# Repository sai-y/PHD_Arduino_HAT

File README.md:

# PHD_Arduino_HAT

Arduino Leonardo HAT for the Raspberry Pi

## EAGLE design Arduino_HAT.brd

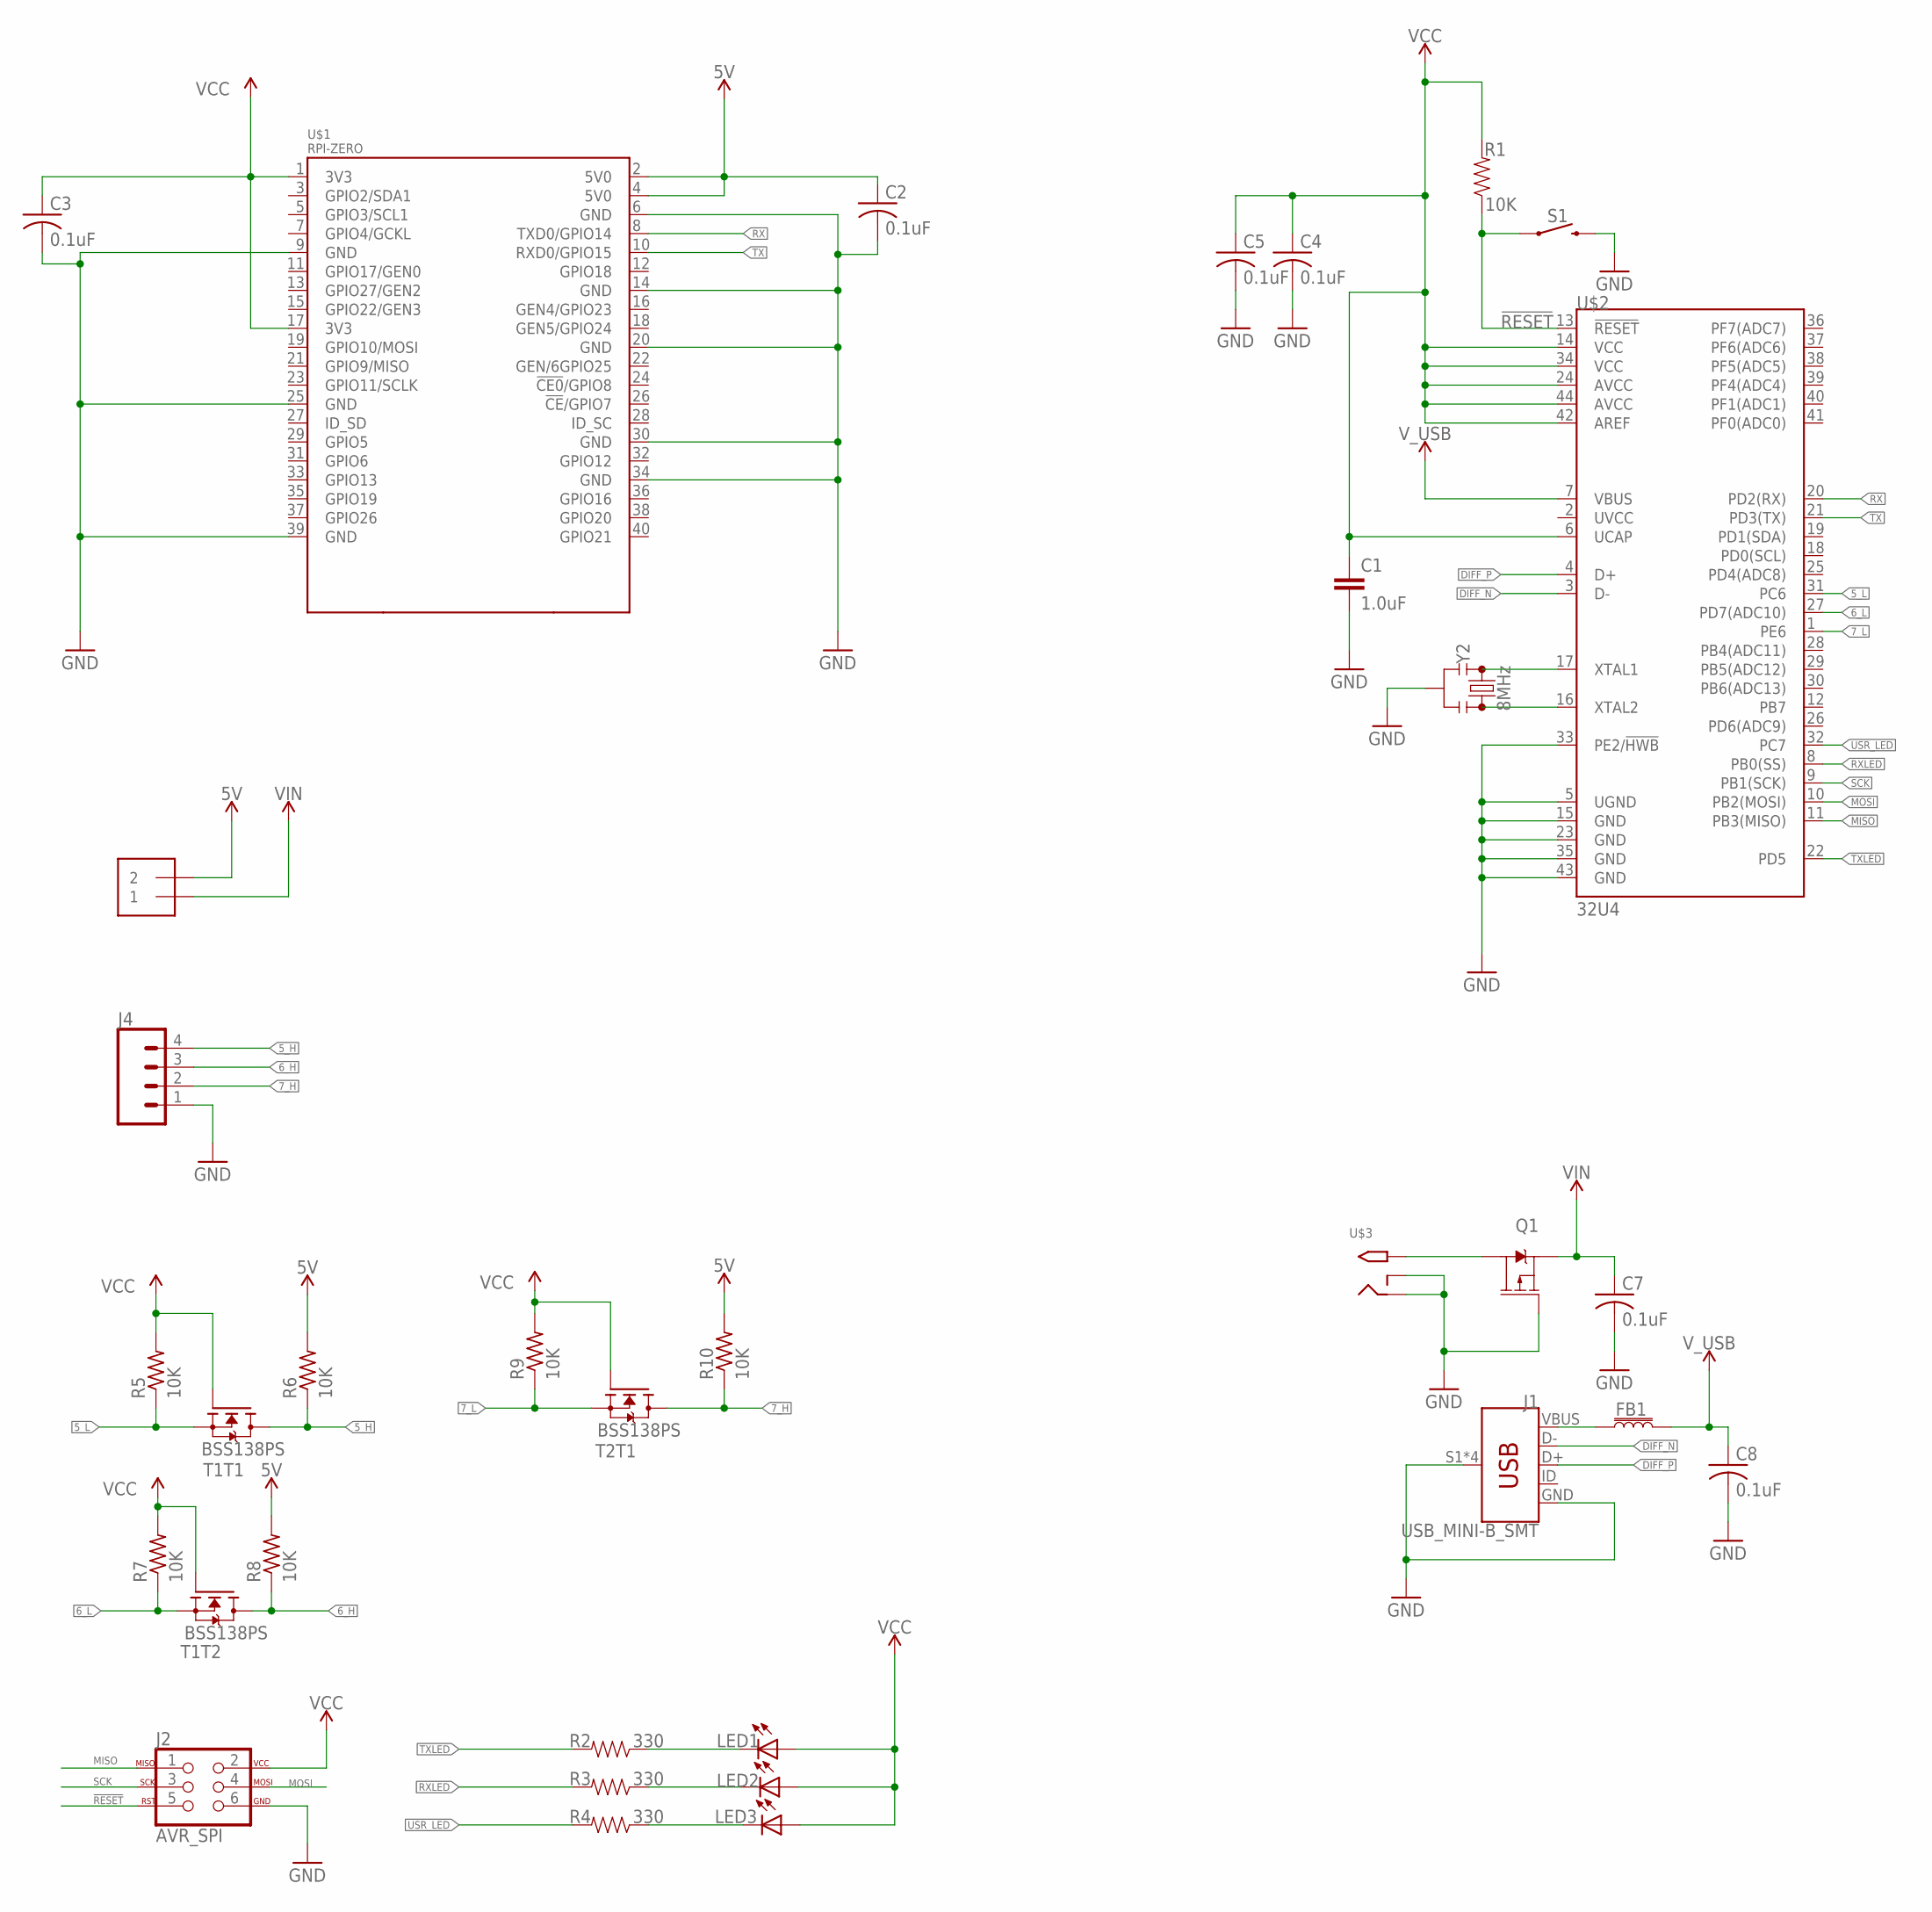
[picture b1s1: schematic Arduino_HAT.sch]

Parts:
C1: 1.0uF; 0805
C2, C3, C4, C5, C7, C8: 0.1uF; C0805
FB1: 30Ω/1.8A; 0603
J1: USB_MINI-B_SMT; USB-MINIB
J2: AVR_SPI; 2X3-NS
J3: 1X2-3.5MM
J4: CONN_04SCREW; SCREWTERMINAL-3.5MM-4
LED1, LED2, LED3: LEDCHIPLED_0805; CHIPLED_0805
Q1: 2.5A/30V/105mΩ; SOT23-3
R1: 10K; 0805
R2, R3, R4: 330; 0805
R5, R6, R7, R8, R9, R10: 10K; R0805
S1: MOMENTARY-SWITCH-SPST-SMD-4.6X2.8MM; TACTILE_SWITCH_SMD_4.6X2.8MM
T1, T2: BSS138PS; SOT363
U$1: RPI-ZERO; RASPBERRYPI_BASTELSTUBE_V13_RASPI_BOARD_B+_FULL
U$2: 32U4; QFN-44
U$3: 2.1MMJACKTHM; PJ-102A
Y2: 8MHz; RESONATOR-SMD-3.2X1.3

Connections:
5V: C2.1, J3.2, R6.2, R8.2, R10.2, U$1.2 (5V0), U$1.4 (5V0)
5_H: J4.4 (GND), R6.1, T1.6 (D)
5_L: R5.1, T1.1 (S), U$2.31 (PC6)
6_H: J4.3 (SDA), R8.1, T1.3 (D)
6_L: R7.1, T1.4 (S), U$2.27 (PD7(ADC10))
7_H: J4.2 (SCL), R10.1, T2.6 (D)
7_L: R9.1, T2.1 (S), U$2.1 (PE6)
!RESET: J2.5, R1.1, S1.1, S1.2 (1), U$2.13 (!RESET)
DIFF_N: J1.D-, U$2.3 (D-)
DIFF_P: J1.D+, U$2.4 (D+)
GND: C1.2, C2.2, C3.2, C4.2, C5.2, C7.2, C8.2, J1.GND, J1.S1 (SHIELD), J1.S2 (SHIELD), J1.S3 (SHIELD), J1.S4 (SHIELD), J2.6, J4.1 (VCC), Q1.1 (G), S1.3 (2), S1.4 (2), U$1.6 (GND), U$1.9 (GND), U$1.14 (GND), U$1.20 (GND), U$1.25 (GND), U$1.30 (GND), U$1.34 (GND), U$1.39 (GND), U$2.5 (UGND), U$2.15 (GND), U$2.23 (GND), U$2.33 (PE2/!HWB), U$2.35 (GND), U$2.43 (GND), U$3.RING, U$3.RING_SW, Y2.2
MISO: J2.1, U$2.11 (PB3(MISO))
MOSI: J2.4, U$2.10 (PB2(MOSI))
unnamed: U$2.16 (XTAL2), Y2.3
unnamed: U$2.17 (XTAL1), Y2.1
unnamed: FB1.1, J1.VBUS
unnamed: Q1.3 (D), U$3.TIP
unnamed: LED1.C, R2.1
unnamed: LED2.C, R3.1
unnamed: LED3.C, R4.1
RX: U$1.8 (TXD0/GPIO14), U$2.20 (PD2(RX))
RXLED: R3.2, U$2.8 (PB0(SS))
SCK: J2.3, U$2.9 (PB1(SCK))
TX: U$1.10 (RXD0/GPIO15), U$2.21 (PD3(TX))
TXLED: R2.2, U$2.22 (PD5)
USR_LED: R4.2, U$2.32 (PC7)
VCC: C1.1, C3.1, C4.1, C5.1, J2.2, LED1.A, LED2.A, LED3.A, R1.2, R5.2, R7.2, R9.2, T1.2 (G), T1.5 (G), T2.2 (G), U$1.1 (3V3), U$1.17 (3V3), U$2.6 (UCAP), U$2.14 (VCC), U$2.24 (AVCC), U$2.34 (VCC), U$2.42 (AREF), U$2.44 (AVCC)
VIN: C7.1, J3.1, Q1.2 (S)
V_USB: C8.1, FB1.2, U$2.7 (VBUS)

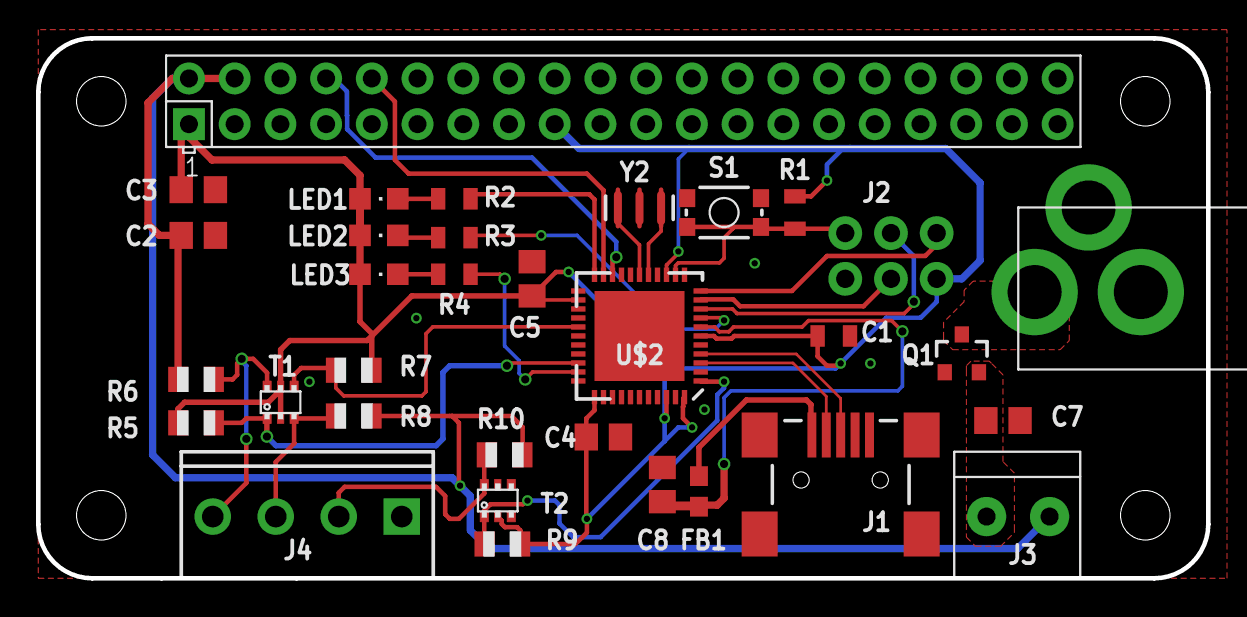
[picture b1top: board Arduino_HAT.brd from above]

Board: 2 copper layers, 65.0 x 30.0 mm, 33 parts (0 on the bottom side), 29 nets.

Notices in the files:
parts and their libraries:
SparkFun-Connectors: Licensing: Creative Commons ShareAlike 4.0 International - https://creativecommons.org/licenses/by-sa/4.0
